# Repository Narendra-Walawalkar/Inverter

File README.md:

# Inverter
PCB designing with schematics file

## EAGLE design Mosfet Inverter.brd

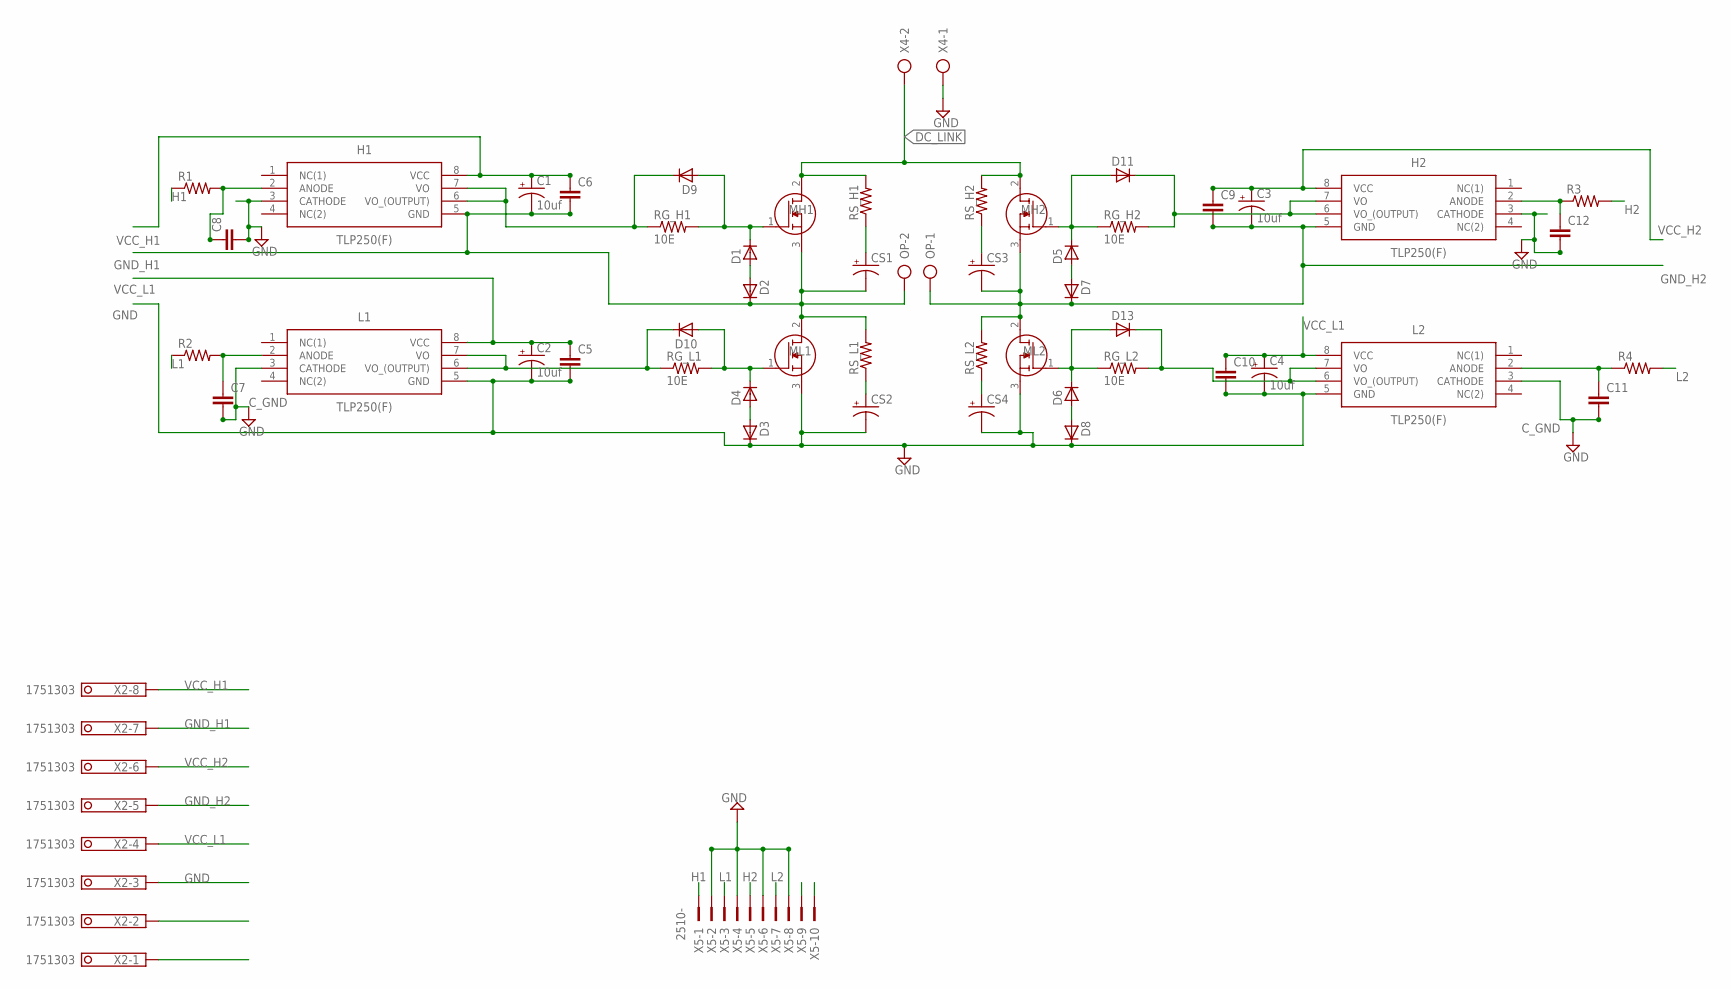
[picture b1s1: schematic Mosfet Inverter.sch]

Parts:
C1, C2, C3, C4: 10uf; E2,5-5
C5, C6, C7, C8, C9, C10, C11, C12: C-EUC1206K; C1206K
CS1, CS2, CS3, CS4: CPOL-USE2.5-5; E2,5-5
D1, D2, D3, D4, D5, D6, D7, D8, D9, D10, D11, D13: PMLL4150; SOD80C
H1, H2: TLP250(F); DIP762W60P254L966H485Q8N
L1, L2: TLP250(F); DIP762W60P254L966H485Q8N
MH1, MH2: RCX100N25; TO254P480X1010X2060-3P
ML1, ML2: RCX100N25; TO254P480X1010X2060-3P
OP: AK300/2
R1, R2, R3, R4: R-US_R1206W; R1206W
RG_H1, RG_H2: 10E; R1206W
RG_L1, RG_L2: 10E; R1206W
RS_H1, RS_H2: R-US_0207/15; 0207/15
RS_L1, RS_L2: R-US_0207/15; 0207/15
X2: 1751303
X4: AK300/2
X5: 2510-; PAK100/2500-10

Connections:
C_GND: C7.2, C8.2, C11.2, C12.2, H1.3 (CATHODE), H2.3 (CATHODE), L1.3 (CATHODE), L2.3 (CATHODE), X5.2, X5.4, X5.6, X5.8
DC_LINK: MH1.2 (DRAIN), MH2.2 (DRAIN), RS_H1.2, RS_H2.2, X4.2
GND: C2.-, C4.-, C5.2, C10.2, CS2.-, CS4.-, D3.C, D8.C, L1.5 (GND), L2.5 (GND), ML1.3 (SOURCE), ML2.3 (SOURCE), X2.3, X4.1
GND_H1: C1.-, C6.2, CS1.-, D2.C, H1.5 (GND), MH1.3 (SOURCE), ML1.2 (DRAIN), OP.2, RS_L1.2, X2.7
GND_H2: C3.-, C9.2, CS3.-, D7.C, H2.5 (GND), MH2.3 (SOURCE), ML2.2 (DRAIN), OP.1, RS_L2.2, X2.5
H1: R1.1, X5.1
H2: R3.2, X5.5
L1: R2.1, X5.3
L2: R4.2, X5.7
unnamed: CS1.+, RS_H1.1
unnamed: D11.C, H2.6 (VO_(OUTPUT)), H2.7 (VO), RG_H2.2
unnamed: C7.1, L1.2 (ANODE), R2.2
unnamed: CS3.+, RS_H2.1
unnamed: CS4.+, RS_L2.1
unnamed: C8.1, H1.2 (ANODE), R1.2
unnamed: CS2.+, RS_L1.1
unnamed: D5.A, D7.A
unnamed: D6.A, D8.A
unnamed: D1.C, D9.A, MH1.1 (GATE), RG_H1.2
unnamed: D1.A, D2.A
unnamed: D13.C, L2.6 (VO_(OUTPUT)), L2.7 (VO), RG_L2.2
unnamed: D3.A, D4.A
unnamed: D4.C, D10.A, ML1.1 (GATE), RG_L1.2
unnamed: D6.C, D13.A, ML2.1 (GATE), RG_L2.1
unnamed: D5.C, D11.A, MH2.1 (GATE), RG_H2.1
unnamed: D9.C, H1.6 (VO_(OUTPUT)), H1.7 (VO), RG_H1.1
unnamed: D10.C, L1.6 (VO_(OUTPUT)), L1.7 (VO), RG_L1.1
unnamed: C12.1, H2.2 (ANODE), R3.1
unnamed: C11.1, L2.2 (ANODE), R4.1
VCC_H1: C1.+, C6.1, H1.8 (VCC), X2.8
VCC_H2: C3.+, C9.1, H2.8 (VCC), X2.6
VCC_L1: C2.+, C4.+, C5.1, C10.1, L1.8 (VCC), L2.8 (VCC), X2.4

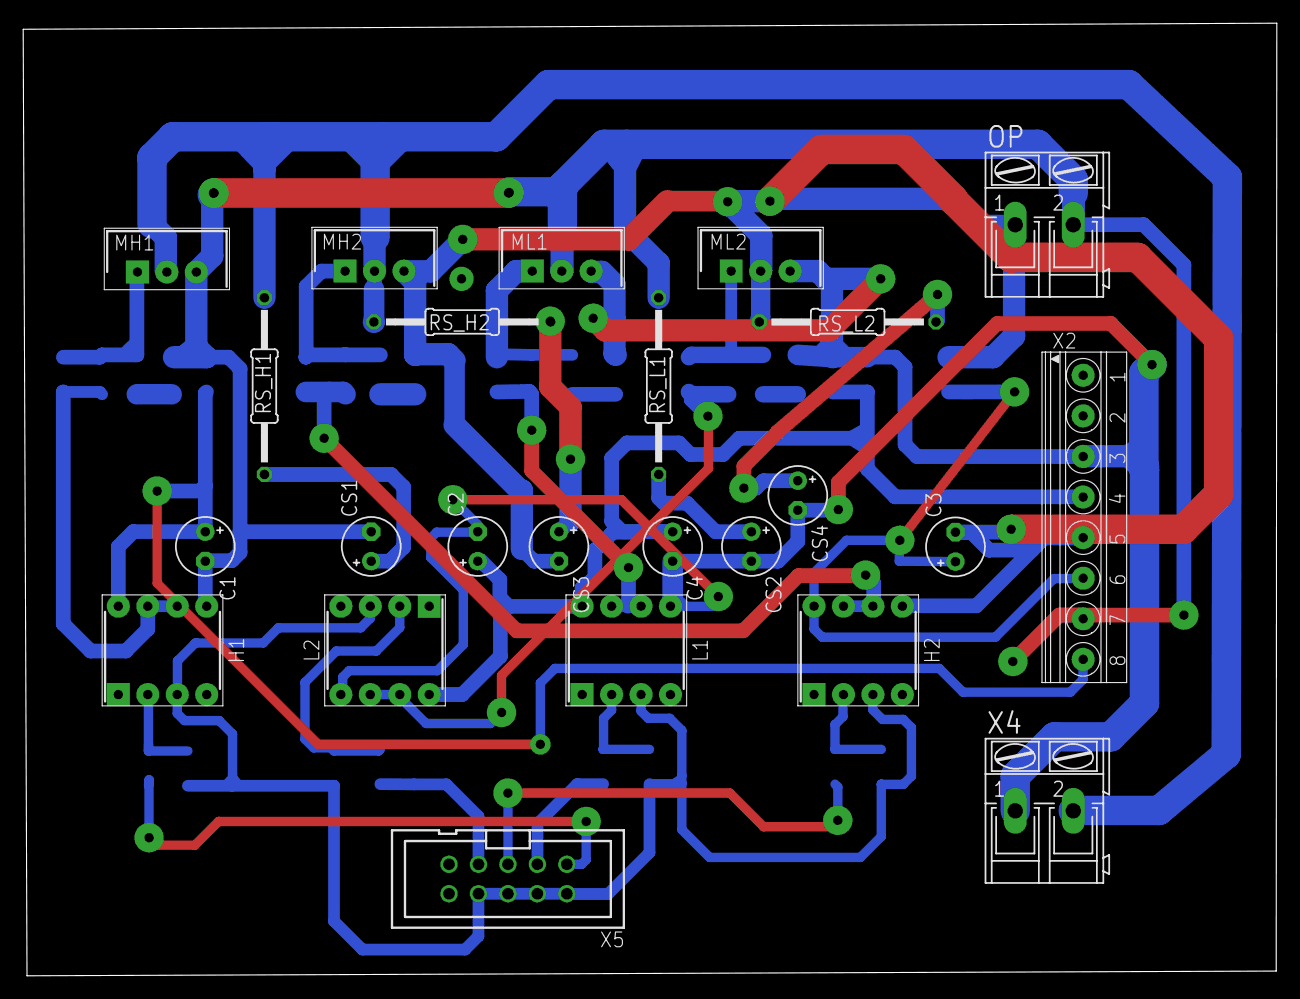
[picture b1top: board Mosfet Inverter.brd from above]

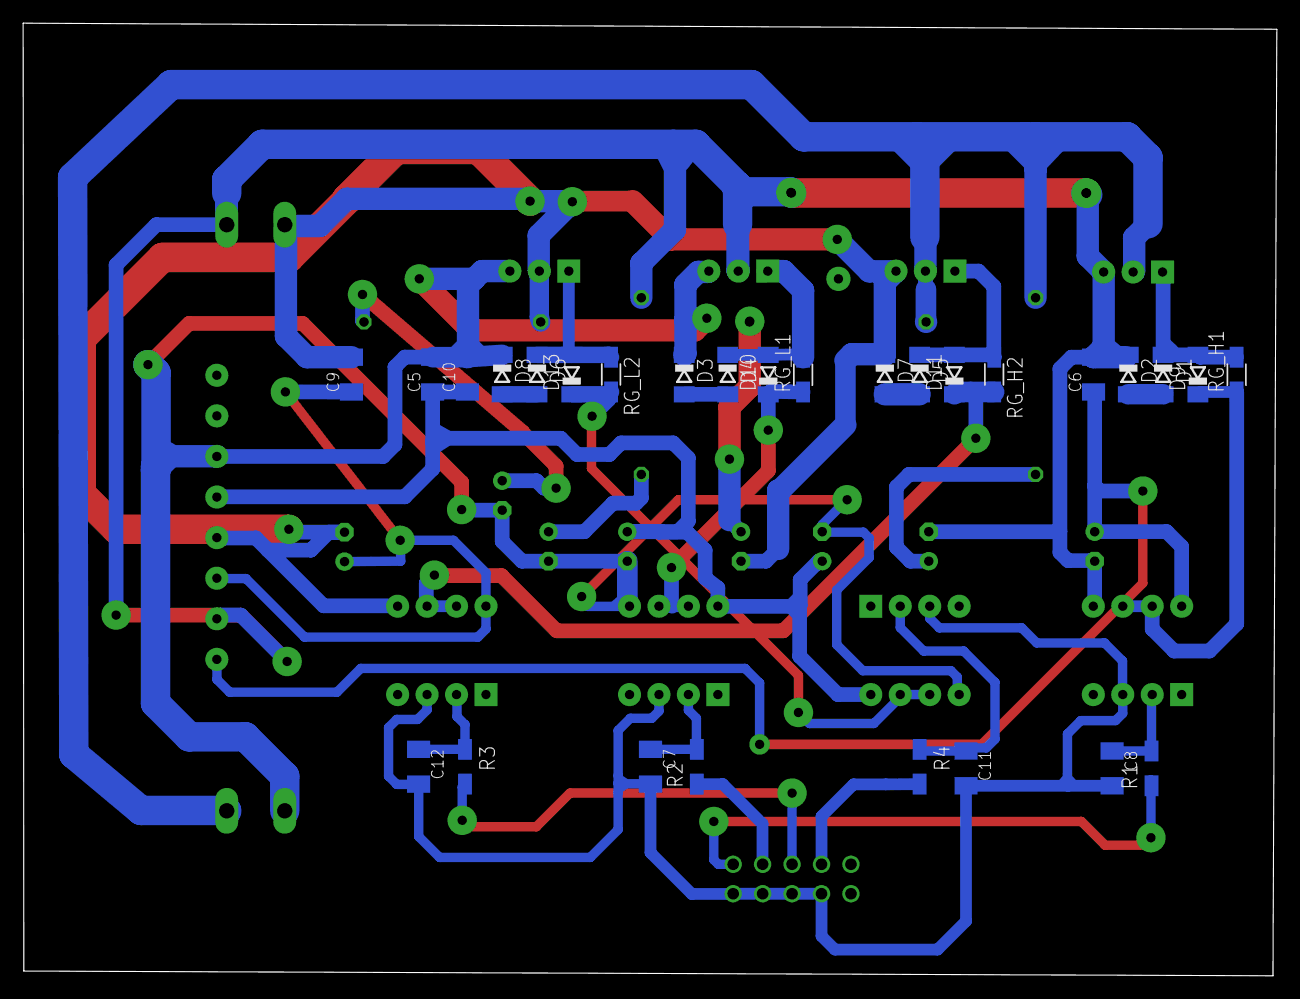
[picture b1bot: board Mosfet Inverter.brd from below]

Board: 2 copper layers, 108.1 x 82.2 mm, 52 parts (28 on the bottom side), 32 nets.

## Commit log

2019-05-19 PCB design of inverter
2019-05-19 Board file for Inverter
2019-05-19 Schematic file for Inverter
